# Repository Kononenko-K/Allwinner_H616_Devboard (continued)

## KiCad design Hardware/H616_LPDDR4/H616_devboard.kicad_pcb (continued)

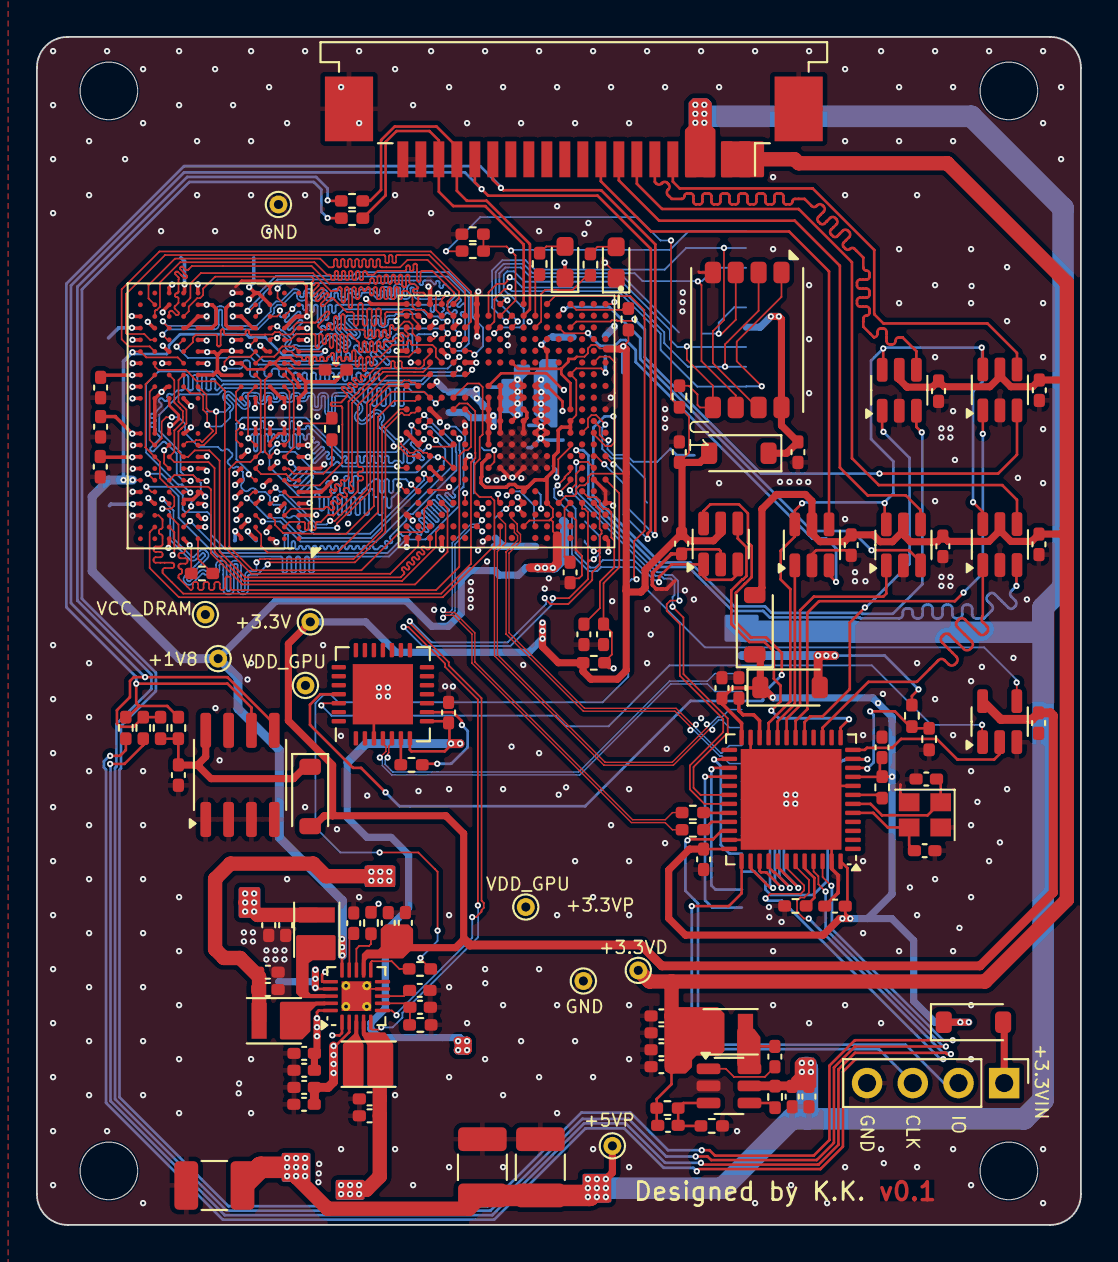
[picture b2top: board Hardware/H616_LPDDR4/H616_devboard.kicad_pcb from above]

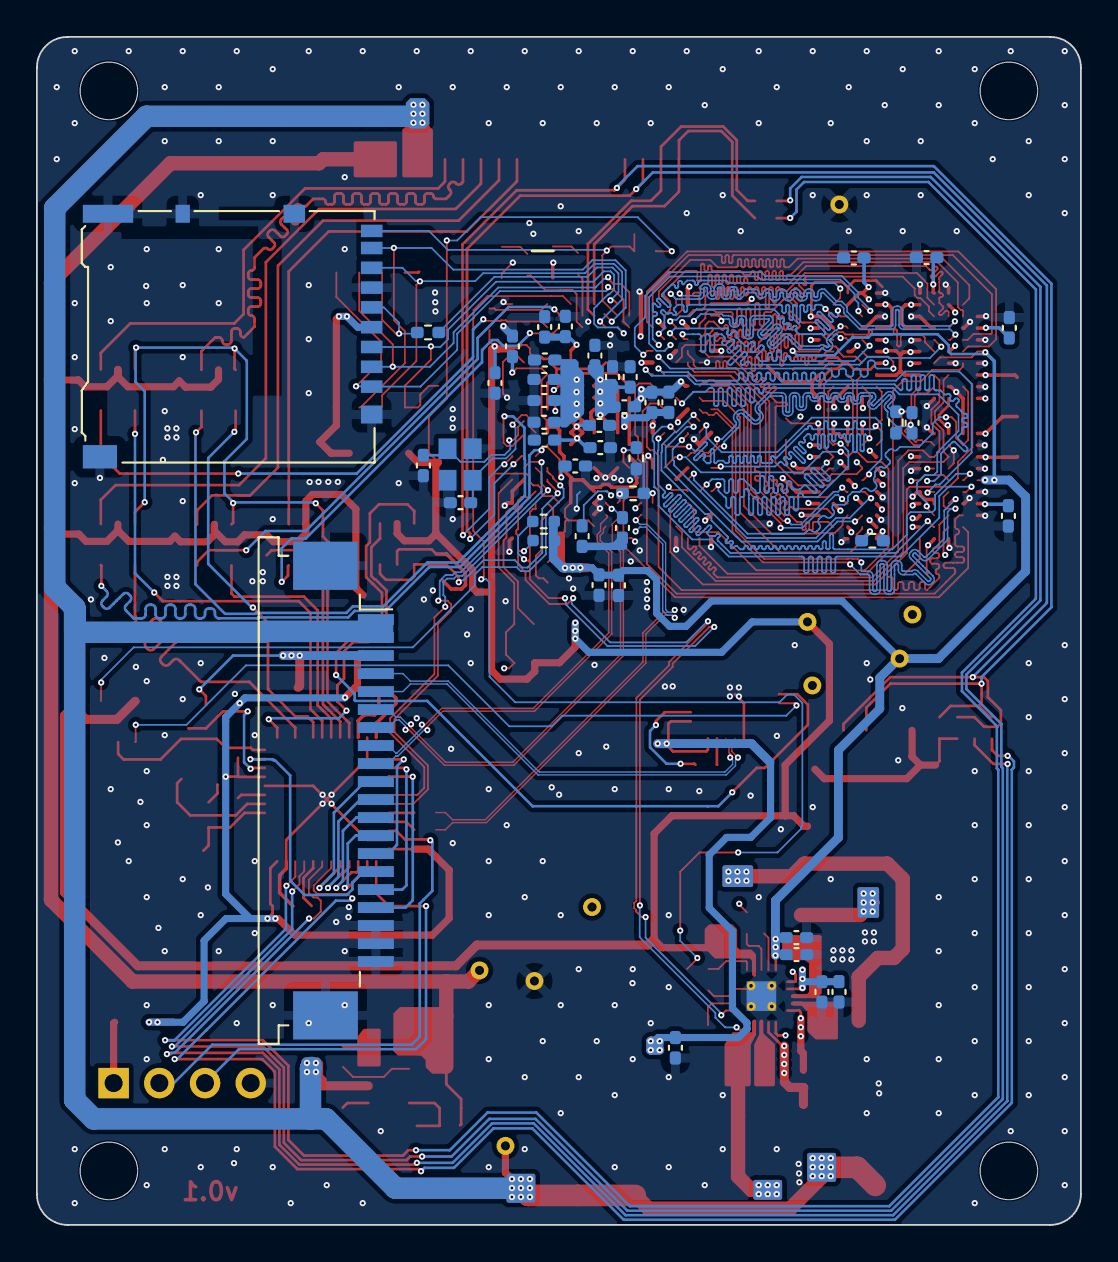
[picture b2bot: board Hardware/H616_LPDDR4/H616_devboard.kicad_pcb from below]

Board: 4 copper layers, 58.0 x 66.0 mm, 165 parts (44 on the bottom side), 174 nets.

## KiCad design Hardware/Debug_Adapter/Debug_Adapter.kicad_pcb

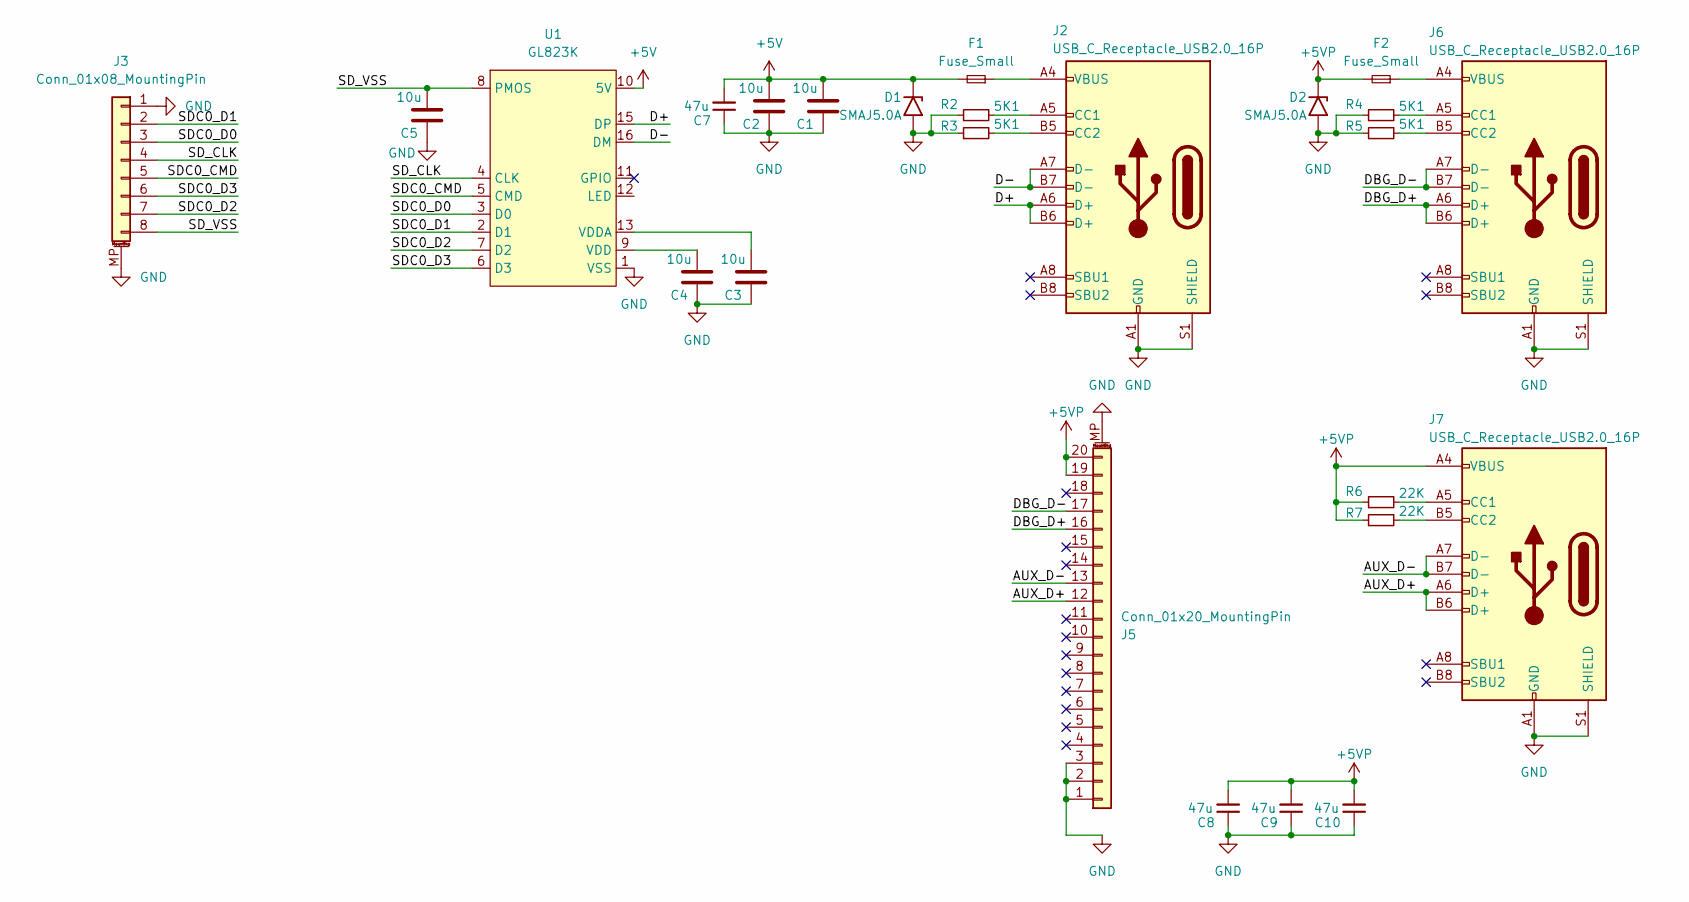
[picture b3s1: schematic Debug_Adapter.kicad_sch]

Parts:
C1, C2, C3, C4, C5: 10u; C_0402_1005Metric_Pad0.74x0.62mm_HandSolder; Part Number GRM155R61A106ME44D
C7, C8, C9, C10: 47u; C_1210_3225Metric_Pad1.33x2.70mm_HandSolder; Part Number CS3225X7R476K160NRL
D1, D2: SMAJ5.0A; D_SMA; Part Number SMAJ5.0A
F1, F2: Fuse_Small; Fuse_1812_4532Metric_Pad1.30x3.40mm_HandSolder; Part Number SMD1812-200C-30V
J2, J6, J7: USB_C_Receptacle_USB2.0_16P; USB_C_Receptacle_GCT_USB4105-xx-A_16P_TopMnt_Horizontal; Part Number TYPE-C-31-M-12
J3: Conn_01x08_MountingPin; TE_84952-8_1x08-1MP_P1.0mm_Horizontal; Part Number XW10202-08R-00
J5: Conn_01x20_MountingPin; TE_2-84952-0_1x20-1MP_P1.0mm_Horizontal; Part Number XW10202-20R-00
R2, R3, R4, R5: 5K1; R_0402_1005Metric; Part Number RC0402FR-075K1L
R6, R7: 22K; R_0402_1005Metric; Part Number RC0402FR-0722KL
U1: GL823K; SSOP-16_3.9x4.9mm_P0.635mm; Part Number Genesys Logic

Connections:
+5V: C1.2, C2.2, C7.2, D1.1 (A1), F1.2, U1.10 (5V)
+5VP: C8.2, C9.2, C10.2, D2.1 (A1), F2.2, J5.19, J5.20, J7.A4 (VBUS), J7.A9 (VBUS), J7.B4 (VBUS), J7.B9 (VBUS), R6.1, R7.1
/AUX_D+: J5.12, J7.A6 (D+), J7.B6 (D+)
/AUX_D-: J5.13, J7.A7 (D-), J7.B7 (D-)
/D+: J2.A6 (D+), J2.B6 (D+), U1.15 (DP)
/D-: J2.A7 (D-), J2.B7 (D-), U1.16 (DM)
/DBG_D+: J5.16, J6.A6 (D+), J6.B6 (D+)
/DBG_D-: J5.17, J6.A7 (D-), J6.B7 (D-)
/SDC0_CMD: J3.5, U1.5 (CMD)
/SDC0_D0: J3.3, U1.3 (D0)
/SDC0_D1: J3.2, U1.2 (D1)
/SDC0_D2: J3.7, U1.7 (D2)
/SDC0_D3: J3.6, U1.6 (D3)
/SD_CLK: J3.4, U1.4 (CLK)
/SD_VSS: C5.2, J3.8, U1.8 (PMOS)
GND: C1.1, C2.1, C3.1, C4.1, C5.1, C7.1, C8.1, C9.1, C10.1, D1.2 (A2), D2.2 (A2), J2.A1 (GND), J2.A12 (GND), J2.B1 (GND), J2.B12 (GND), J2.S1 (SHIELD), J3.1, J3.MP (MountPin), J5.1, J5.2, J5.3, J5.MP (MountPin), J6.A1 (GND), J6.A12 (GND), J6.B1 (GND), J6.B12 (GND), J6.S1 (SHIELD), J7.A1 (GND), J7.A12 (GND), J7.B1 (GND), J7.B12 (GND), J7.S1 (SHIELD), R2.1, R3.1, R4.1, R5.1, U1.1 (VSS), U1.14 (VSS)
unnamed: F1.1, J2.A4 (VBUS), J2.A9 (VBUS), J2.B4 (VBUS), J2.B9 (VBUS)
unnamed: F2.1, J6.A4 (VBUS), J6.A9 (VBUS), J6.B4 (VBUS), J6.B9 (VBUS)
unnamed: J2.A5 (CC1), R2.2
unnamed: J2.B5 (CC2), R3.2
unnamed: J6.A5 (CC1), R4.2
unnamed: J6.B5 (CC2), R5.2
unnamed: J7.A5 (CC1), R6.2
unnamed: J7.B5 (CC2), R7.2
unnamed: C4.2, U1.9 (VDD)
unnamed: C3.2, U1.13 (VDDA)

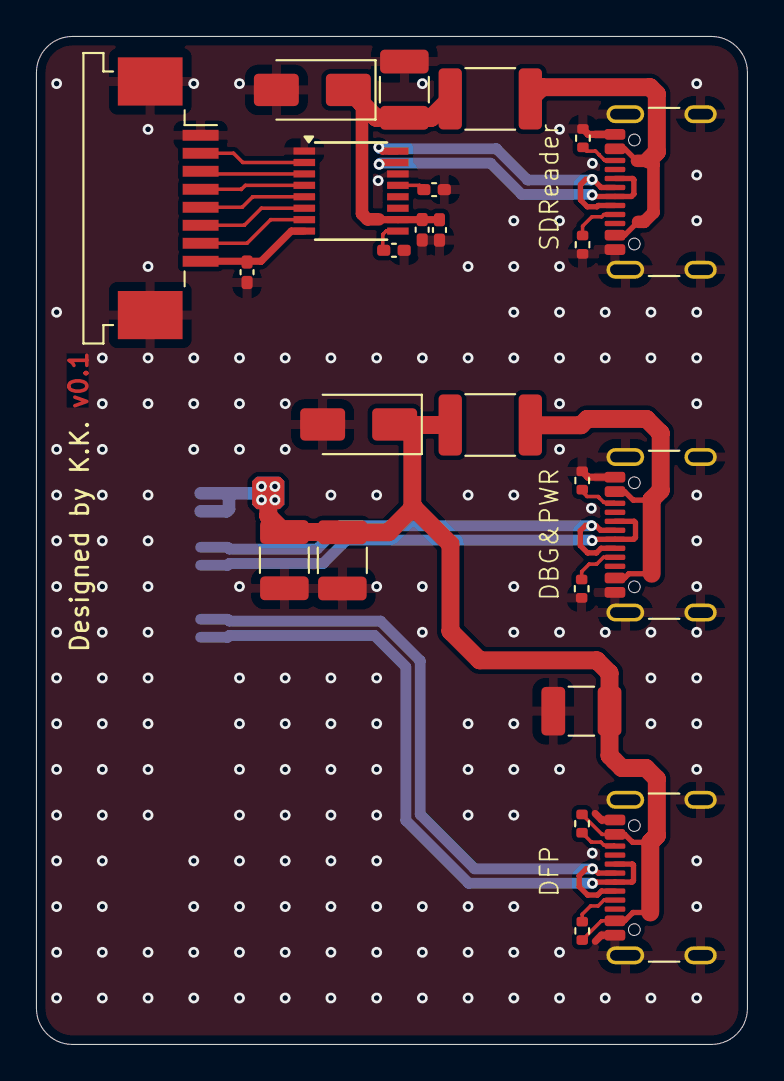
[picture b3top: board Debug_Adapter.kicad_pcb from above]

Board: 2 copper layers, 39.5 x 56.0 mm, 25 parts (1 on the bottom side), 26 nets.

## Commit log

2023-10-23 init
2024-04-18 fixed crystal resonator value
2025-07-04 Added license information
2026-02-14 Add new board version with LPDDR4
2026-02-14 Fix path to license file
